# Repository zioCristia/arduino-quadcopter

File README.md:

# Arduino quadcopter
Arduino based quadcopter made, using MultiWii FC software and an home-made 3D printed frame.

More will arrive soon!

In the meanwhile you can see the full [YouTube playlist](https://youtube.com/playlist?list=PL9vSZB3pcT72WKoZpo7NASmBoKJBsFOGY) (in italian).

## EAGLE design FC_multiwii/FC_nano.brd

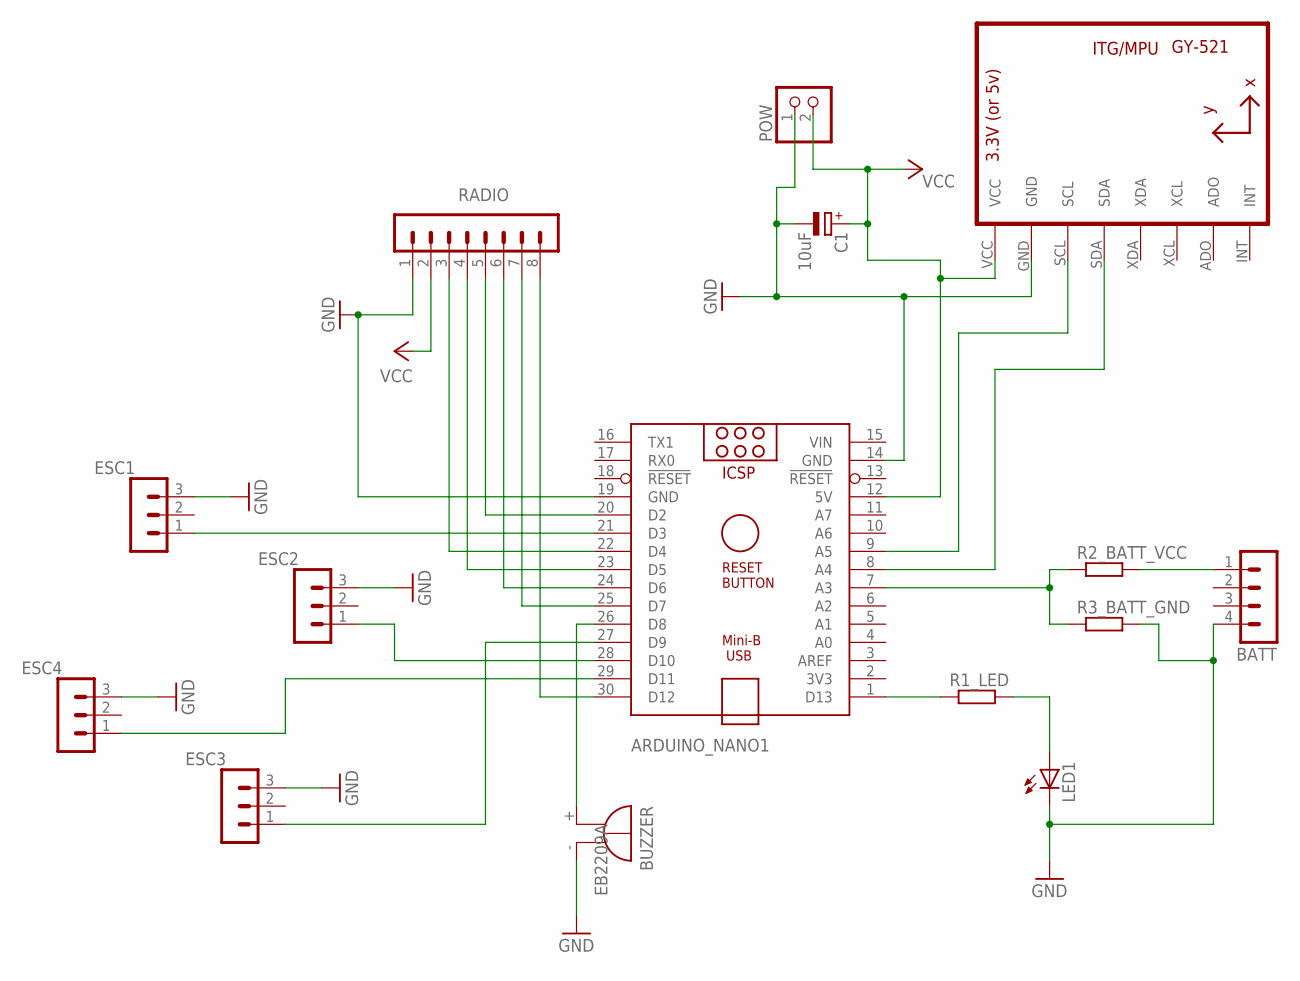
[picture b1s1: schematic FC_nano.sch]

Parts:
ARDUINO_NANO1: ARDUINO_NANO
BATT: MA04-1
BUZZER: EB2209A
C1: 10uF; E2-5
ESC1, ESC2, ESC3, ESC4: MA03-1
LED1: LED3MM
POW: PINHD-1X2; 1X02
R1_LED, R2_BATT_VCC, R3_BATT_GND: R-EU_0204/7; 0204/7
RADIO: MA08-1
U1: GY-521MPU6050; GY-521

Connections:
GND: ARDUINO_NANO1.14 (GND), ARDUINO_NANO1.19 (GND), BATT.4, BUZZER.-, C1.-, ESC1.3, ESC2.3, ESC3.3, ESC4.3, LED1.K (C), POW.1, R3_BATT_GND.2, RADIO.1, U1.GND
unnamed: ARDUINO_NANO1.21 (D3), ESC1.1
unnamed: ARDUINO_NANO1.28 (D10), ESC2.1
unnamed: ARDUINO_NANO1.27 (D9), ESC3.1
unnamed: ARDUINO_NANO1.29 (D11), ESC4.1
unnamed: ARDUINO_NANO1.1 (D13), R1_LED.1
unnamed: ARDUINO_NANO1.20 (D2), RADIO.5
unnamed: ARDUINO_NANO1.22 (D4), RADIO.3
unnamed: ARDUINO_NANO1.23 (D5), RADIO.4
unnamed: ARDUINO_NANO1.24 (D6), RADIO.6
unnamed: ARDUINO_NANO1.8 (A4), U1.SDA
unnamed: ARDUINO_NANO1.9 (A5), U1.SCL
unnamed: ARDUINO_NANO1.25 (D7), RADIO.7
unnamed: LED1.A, R1_LED.2
unnamed: ARDUINO_NANO1.30 (D12), RADIO.8
unnamed: ARDUINO_NANO1.26 (D8), BUZZER.+
unnamed: BATT.1, R2_BATT_VCC.2
unnamed: ARDUINO_NANO1.7 (A3), R2_BATT_VCC.1, R3_BATT_GND.1
VCC: ARDUINO_NANO1.12 (5V), C1.+, POW.2, RADIO.2, U1.VCC
VIN: ARDUINO_NANO1.15 (VIN)

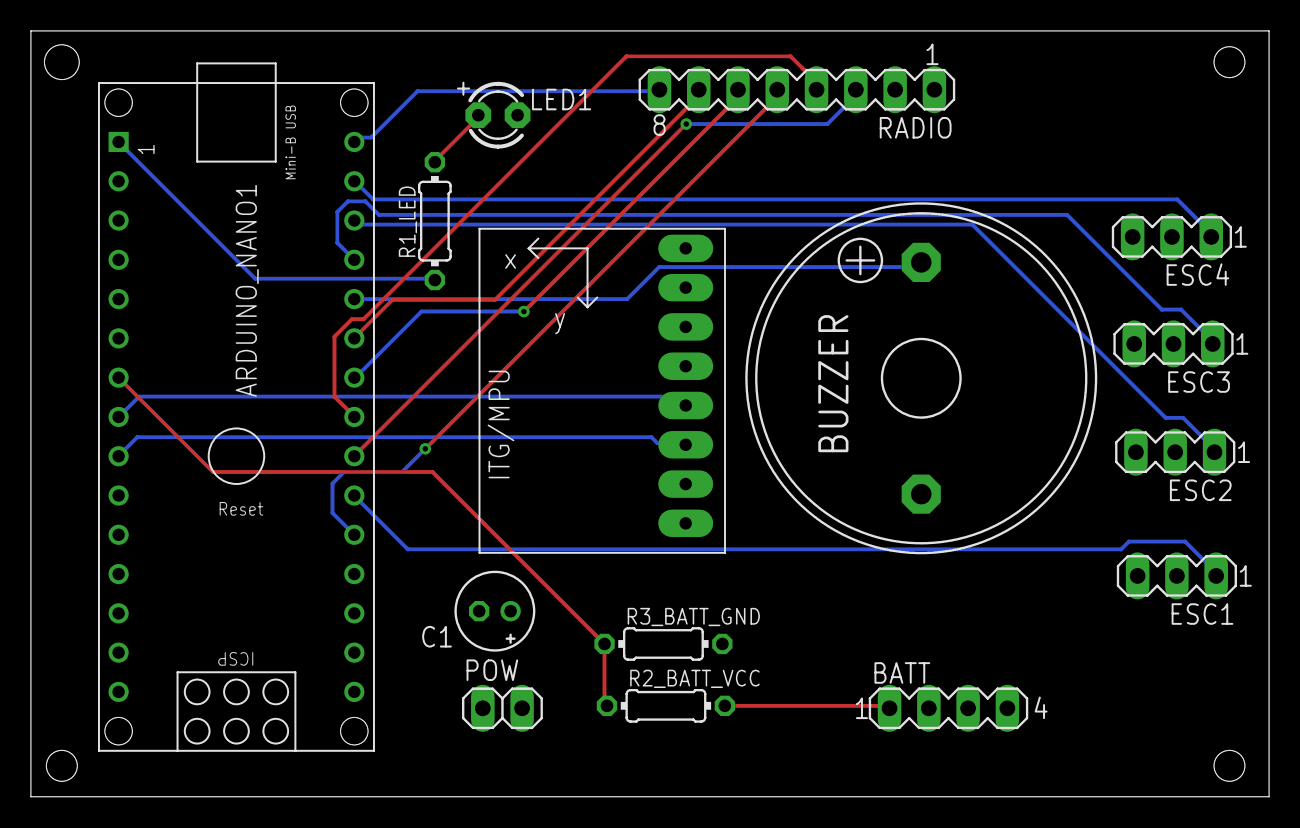
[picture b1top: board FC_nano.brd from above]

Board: 2 copper layers, 80.1 x 49.5 mm, 15 parts (0 on the bottom side), 19 nets.

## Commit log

2022-07-14 Upload software of flight controller
2025-03-23 Add FC pcb files
